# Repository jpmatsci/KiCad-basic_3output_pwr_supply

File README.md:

# KiCad-basic_3output_pwr_supply
This is a basic power supply for 12V, 5V, and 3.3V that I made for prototyping with KiCad.

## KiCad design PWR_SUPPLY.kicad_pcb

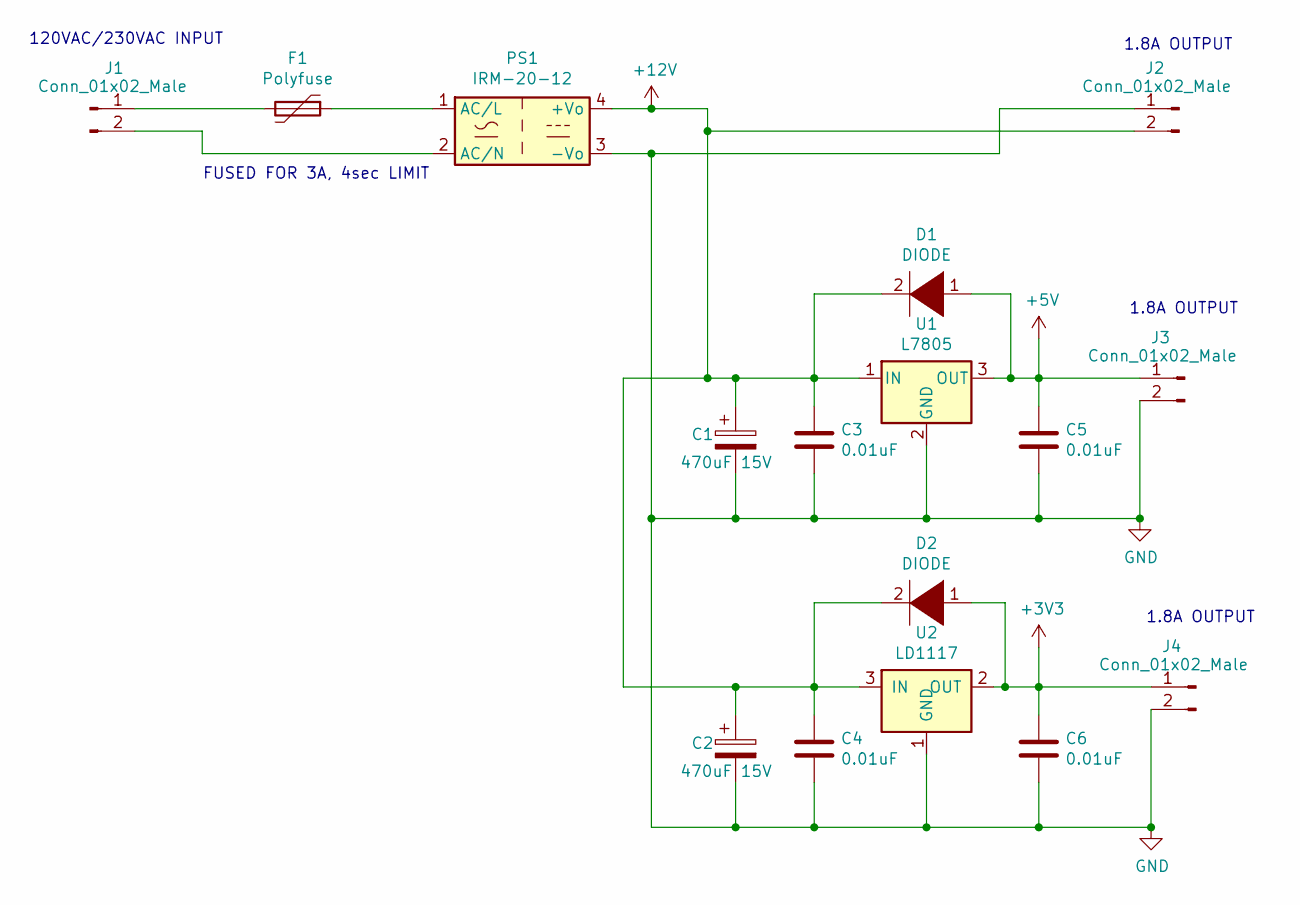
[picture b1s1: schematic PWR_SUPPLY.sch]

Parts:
C1, C2: 470uF 15V; CP_Elec_4x3.9; Part PCE3909DKR-ND
C3, C4, C5, C6: 0.01uF; C_0805_2012Metric; Part 478-1395-6-ND
D1, D2: DIODE; D_SOD-123; Part 1N4148W-FDIDKR-ND
F1: Polyfuse; Fuse_Bourns_MF-RG500; Part TRF600-150-2TR-ND
J1, J2, J3, J4: Conn_01x02_Male; TerminalBlock_bornier-2_P5.08mm; Part A113320-ND
PS1: IRM-20-12; Converter_ACDC_MeanWell_IRM-20-xx_THT; Part 1866-3038-ND
U1: L7805; TO-252-3_TabPin2; Part 497-7255-2-ND
U2: LD1117; TO-252-3_TabPin2; Part 497-3455-6-ND

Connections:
+3V3: C6.1, D2.1 (K), J4.1, U2.2 (OUT)
+5V: C5.1, D1.1 (K), J3.1, U1.3 (OUT)
+12V: C1.1, C2.1, C3.1, C4.1, D1.2 (A), D2.2 (A), J2.2, PS1.4 (+Vo), U1.1 (IN), U2.3 (IN)
GND: C1.2, C2.2, C3.2, C4.2, C5.2, C6.2, J2.1, J3.2, J4.2, PS1.3 (-Vo), U1.2 (GND), U2.1 (GND)
unnamed: F1.1, PS1.1 (AC/L)
unnamed: F1.2, J1.1
unnamed: J1.2, PS1.2 (AC/N)

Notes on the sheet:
1.8A OUTPUT
120VAC/230VAC INPUT
FUSED FOR 3A, 4sec LIMIT

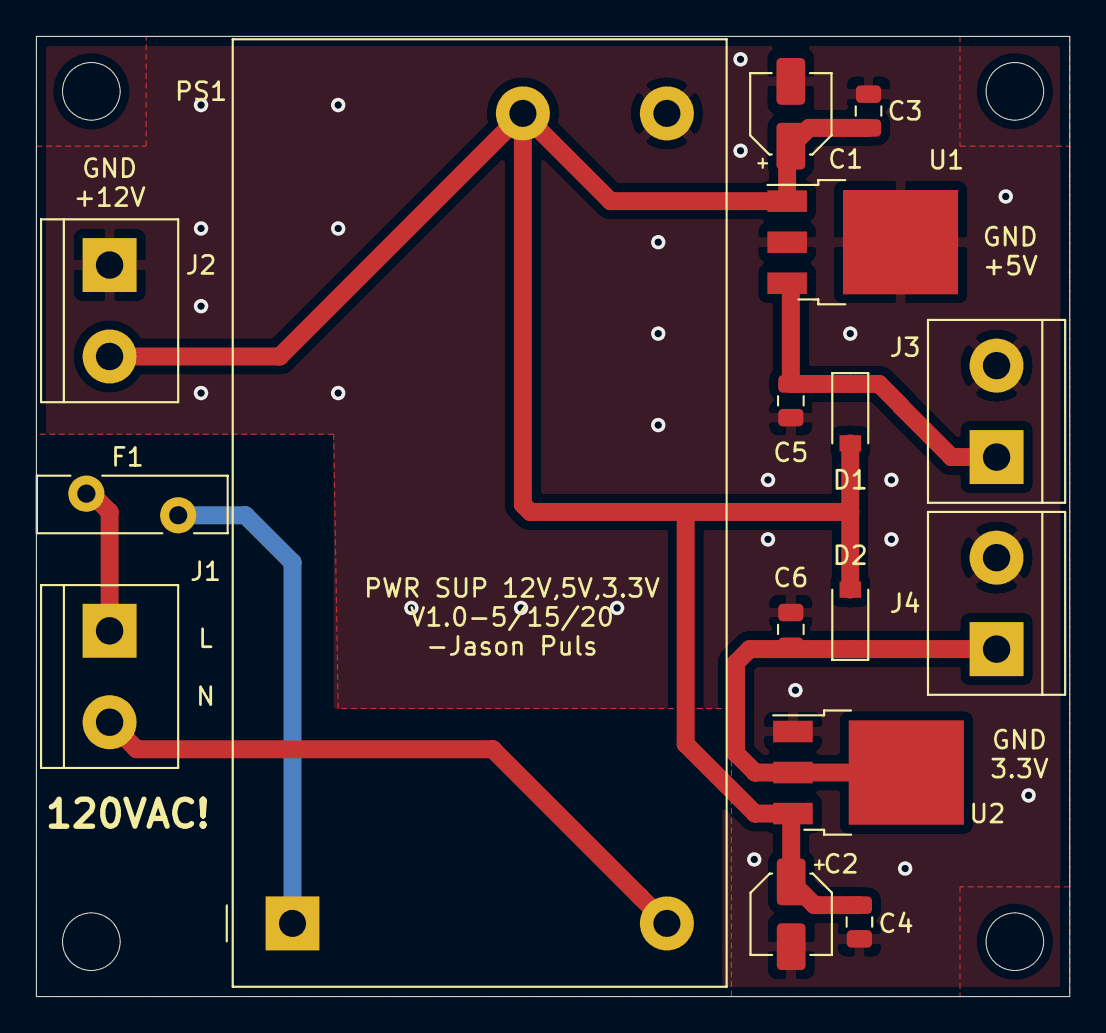
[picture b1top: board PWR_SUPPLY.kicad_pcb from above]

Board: 2 copper layers, 57.4 x 53.3 mm, 16 parts (0 on the bottom side), 7 nets.

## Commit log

2020-05-21 First Commit
    This is a basic power supply using an IRM-20-12 for 12V and 78XXs for 5V and 3.3V. Taught me some KiCad.
